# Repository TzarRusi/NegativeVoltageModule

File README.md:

**Автор: Владислав Чернухин** · [Инженерное портфолио](https://github.com/TzarRusi)

Специализированная четырёхканальная плата отрицательного питания для лабораторных задач. Мой вклад — разработка схемотехники и топологии платы на LT3090. В репозитории собраны редактируемые исходники, схема, BOM и материалы конструктива.

## Фотография платы

<sub>Фото платы с маркировкой HP V0.1, до монтажа компонентов. Разводка отличается от архивной CAD-ревизии, представленной ниже.</sub>

## CAD-ревизия

<sub>Рендер из исходного файла KiCad. Это визуализация PCB; часть компонентов не имеет подключённых 3D-моделей.</sub>

## Устройство

| Узел | Реализация в проекте |
|---|---|
| Каналы | 4 повторяемых иерархических листа Channel0–Channel3 |
| Регулятор | LT3090EMSE_PBF, корпус MSOP-12 с теплоотводящей площадкой |
| Настройка | Потенциометры в каждом канале |
| Контроль | Подключения внешних вольтметров и амперметров |
| Выходы | 4 коаксиальных разъёма SMA |
| PCB | 2 медных слоя; толщина платы в исходнике 1,57 мм |
| Конструктив | STEP-модели платы и исходники деталей/сборок SolidWorks |

## Схемы и разводка

[Общая схема](NegativeVoltageModule.svg) · [Схема одного канала](NegativeVoltageModule-Channel0.svg) · [Верхний слой PCB](pcb-top.svg)

## Открыть проект

1. Скачайте репозиторий целиком и откройте `NegativeVoltageModule.kicad_pro` в KiCad (исходный формат — KiCad 7; просмотр и экспорт проверены в KiCad 10).
2. Для редактирования библиотечных компонентов распакуйте `custom-library.zip` **в корень репозитория**, сохранив структуру. В архиве находятся локальные таблицы библиотек и посадочное место; символ LT3090 уже включён в репозиторий.
3. Если старые 3D-ссылки не разрешаются, задайте `KICAD6_3DMODEL_DIR` на каталог стандартных 3D-моделей установленного KiCad.
4. Конструктив находится в `mechanical-source.zip`. Для сборок SolidWorks может потребоваться переуказание ссылок на файлы деталей и платы.

| Файлы | Содержание |
|---|---|
| `*.kicad_pro`, `*.kicad_pcb`, `*.kicad_sch` | Проект, плата и иерархическая схема |
| `NegativeVoltageModule.csv` | Исходный BOM; разделитель `;` |
| `LT3090EMSE_PBF.kicad_sym`, `MSOP-12_MSE.kicad_mod` | Пользовательский символ и посадочное место |
| `custom-library.zip` | Локальная конфигурация библиотек для переноса проекта |
| `mechanical-source.zip` | STEP, SLDPRT и SLDASM |
| `manufacturing-review.zip` | Gerber, Excellon Drill, позиции компонентов и BOM для инженерной проверки |
| `VERIFICATION.md` | Результаты проверки и границы готовности |

## Статус

Разработка платы завершена. Исходные схемы, PCB и производственные файлы опубликованы в репозитории.

Справочная документация: [LT3090 — Analog Devices](https://www.analog.com/en/products/lt3090.html). Параметры микросхемы не следует приравнивать к измеренным параметрам всей платы.

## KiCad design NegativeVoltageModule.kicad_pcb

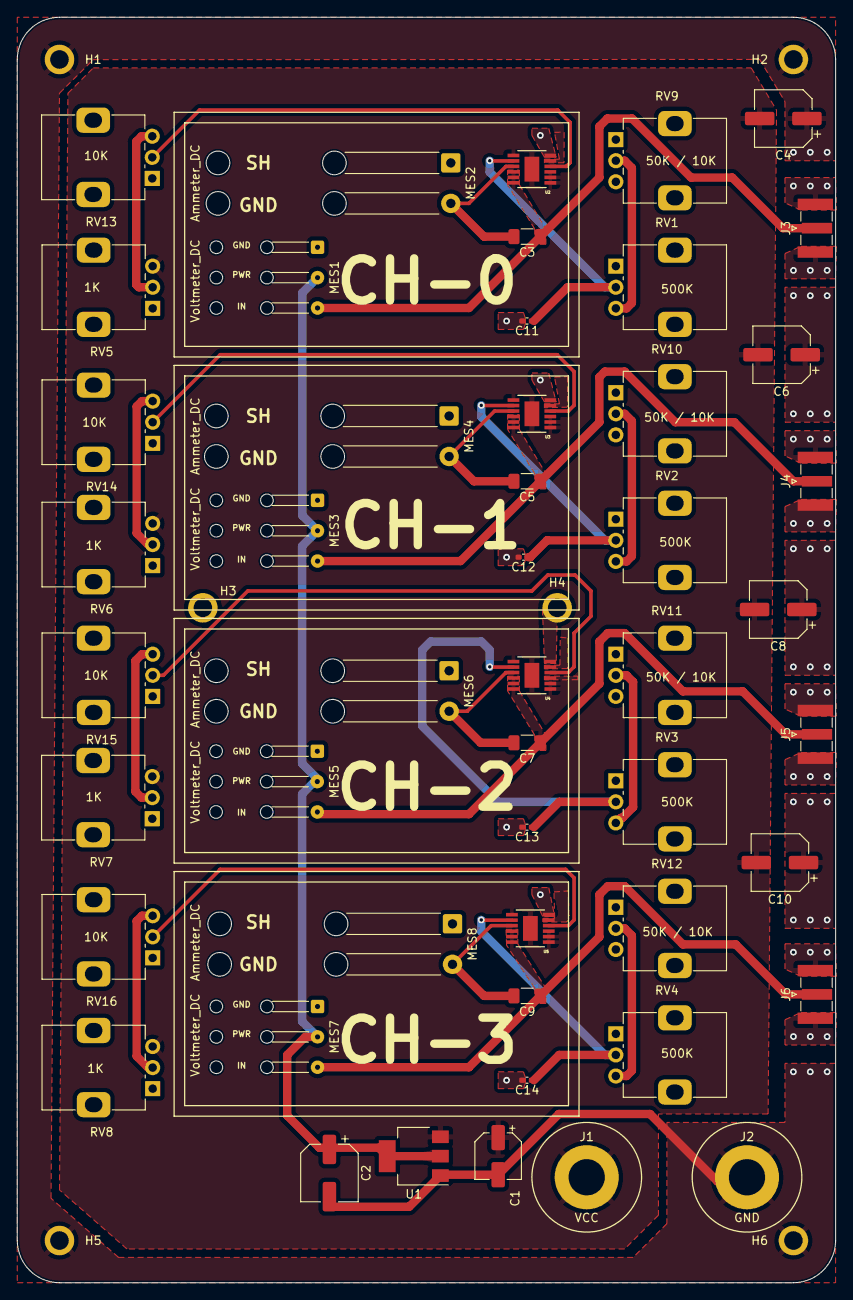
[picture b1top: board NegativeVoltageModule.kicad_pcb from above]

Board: 2 copper layers, 97.0 x 150.0 mm, 55 parts (0 on the bottom side), 27 nets.

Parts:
C1: 10u 35V; CP_Elec_5x5.4
C2, C4, C6, C8, C10: 22u 35V; CP_Elec_6.3x5.4
C3, C5, C7, C9: 10u; C_1206_3216Metric_Pad1.33x1.80mm_HandSolder
C11, C12, C13, C14: 0.1u; C_0402_1005Metric_Pad0.74x0.62mm_HandSolder
H1, H2, H3, H4, H5, H6: MountingHole_Pad; MountingHole_2.2mm_M2_ISO7380_Pad
J1: VCC; MountingHole_4.3mm_M4_ISO7380_Pad
J2: GND; MountingHole_4.3mm_M4_ISO7380_Pad
J3, J4, J5, J6: Conn_Coaxial; SMA_Samtec_SMA-J-P-X-ST-EM1_EdgeMount
MES1, MES3, MES5, MES7: Voltmeter_DC; SolderWire-0.1sqmm_1x03_P3.6mm_D0.4mm_OD1mm_Relief2x
MES2, MES4, MES6, MES8: Ammeter_DC; SolderWire-0.5sqmm_1x02_P4.8mm_D0.9mm_OD2.3mm_Relief2x
RV1, RV2, RV3, RV4: Rv09 500k; Potentiometer_Alps_RK09K_Single_Vertical
RV5, RV6, RV7, RV8: R-09 1K; Potentiometer_Alps_RK09K_Single_Vertical
RV9, RV10, RV11, RV12, RV13, RV14, RV15, RV16: Rv09 10k; Potentiometer_Alps_RK09K_Single_Vertical
U1: AMS1117-5.0; SOT-223-3_TabPin2
U2, U3, U4, U5: LT3090EMSE_PBF; MSOP-12_MSE

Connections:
+5V: C2.1, MES1.2 (PWR), MES3.2 (PWR), MES5.2 (PWR), MES7.2 (PWR), U1.2 (VO)
/Channel0/OUT: C3.1, J3.1 (In), MES1.3 (+), U2.10 (OUT_2), U2.11 (OUT_3), U2.12 (OUT)
/Channel0/SH: J3.2 (Ext), MES2.1 (+)
/Channel1/OUT: C5.1, J4.1 (In), MES3.3 (+), U3.10 (OUT_2), U3.11 (OUT_3), U3.12 (OUT)
/Channel1/SH: J4.2 (Ext), MES4.1 (+)
/Channel2/OUT: C7.1, J5.1 (In), MES5.3 (+), U4.10 (OUT_2), U4.11 (OUT_3), U4.12 (OUT)
/Channel2/SH: J5.2 (Ext), MES6.1 (+)
/Channel3/OUT: C9.1, J6.1 (In), MES7.3 (+), U5.10 (OUT_2), U5.11 (OUT_3), U5.12 (OUT)
/Channel3/SH: J6.2 (Ext), MES8.1 (+)
GND: C1.2, C2.2, C3.2, C4.1, C5.2, C6.1, C7.2, C8.1, C9.2, C10.1, C11.2, C12.2, C13.2, C14.2, H1.1, H2.1, H3.1, H4.1, H5.1, H6.1, J2.1, MES1.1 (-), MES2.2 (-), MES3.1 (-), MES4.2 (-), MES5.1 (-), MES6.2 (-), MES7.1 (-), MES8.2 (-), RV9.3, RV10.3, RV11.3, RV12.3, U1.1 (GND), U2.6 (IMONN), U2.9 (GND), U3.6 (IMONN), U3.9 (GND), U4.6 (IMONN), U4.9 (GND), U5.6 (IMONN), U5.9 (GND)
unnamed: RV1.3, RV9.2
unnamed: RV2.3, RV10.2
unnamed: RV3.3, RV11.2
unnamed: RV4.3, RV12.2
unnamed: RV5.2, RV13.3
unnamed: RV6.2, RV14.3
unnamed: RV7.2, RV15.3
unnamed: RV8.2, RV16.3
unnamed: RV13.2, U2.4 (ILIM)
unnamed: C11.1, RV1.2, U2.8 (SET)
unnamed: RV14.2, U3.4 (ILIM)
unnamed: C12.1, RV2.2, U3.8 (SET)
unnamed: RV15.2, U4.4 (ILIM)
unnamed: C13.1, RV3.2, U4.8 (SET)
unnamed: RV16.2, U5.4 (ILIM)
unnamed: C14.1, RV4.2, U5.8 (SET)
VCC: C1.1, C4.2, C6.2, C8.2, C10.2, J1.1, RV5.3, RV6.3, RV7.3, RV8.3, U1.3 (VI), U2.1 (IN_2), U2.2 (IN_3), U2.3 (IN_4), U2.5 (IMONP), U2.7 (*SHDN), U2.13 (IN), U3.1 (IN_2), U3.2 (IN_3), U3.3 (IN_4), U3.5 (IMONP), U3.7 (*SHDN), U3.13 (IN), U4.1 (IN_2), U4.2 (IN_3), U4.3 (IN_4), U4.5 (IMONP), U4.7 (*SHDN), U4.13 (IN), U5.1 (IN_2), U5.2 (IN_3), U5.3 (IN_4), U5.5 (IMONP), U5.7 (*SHDN), U5.13 (IN)
